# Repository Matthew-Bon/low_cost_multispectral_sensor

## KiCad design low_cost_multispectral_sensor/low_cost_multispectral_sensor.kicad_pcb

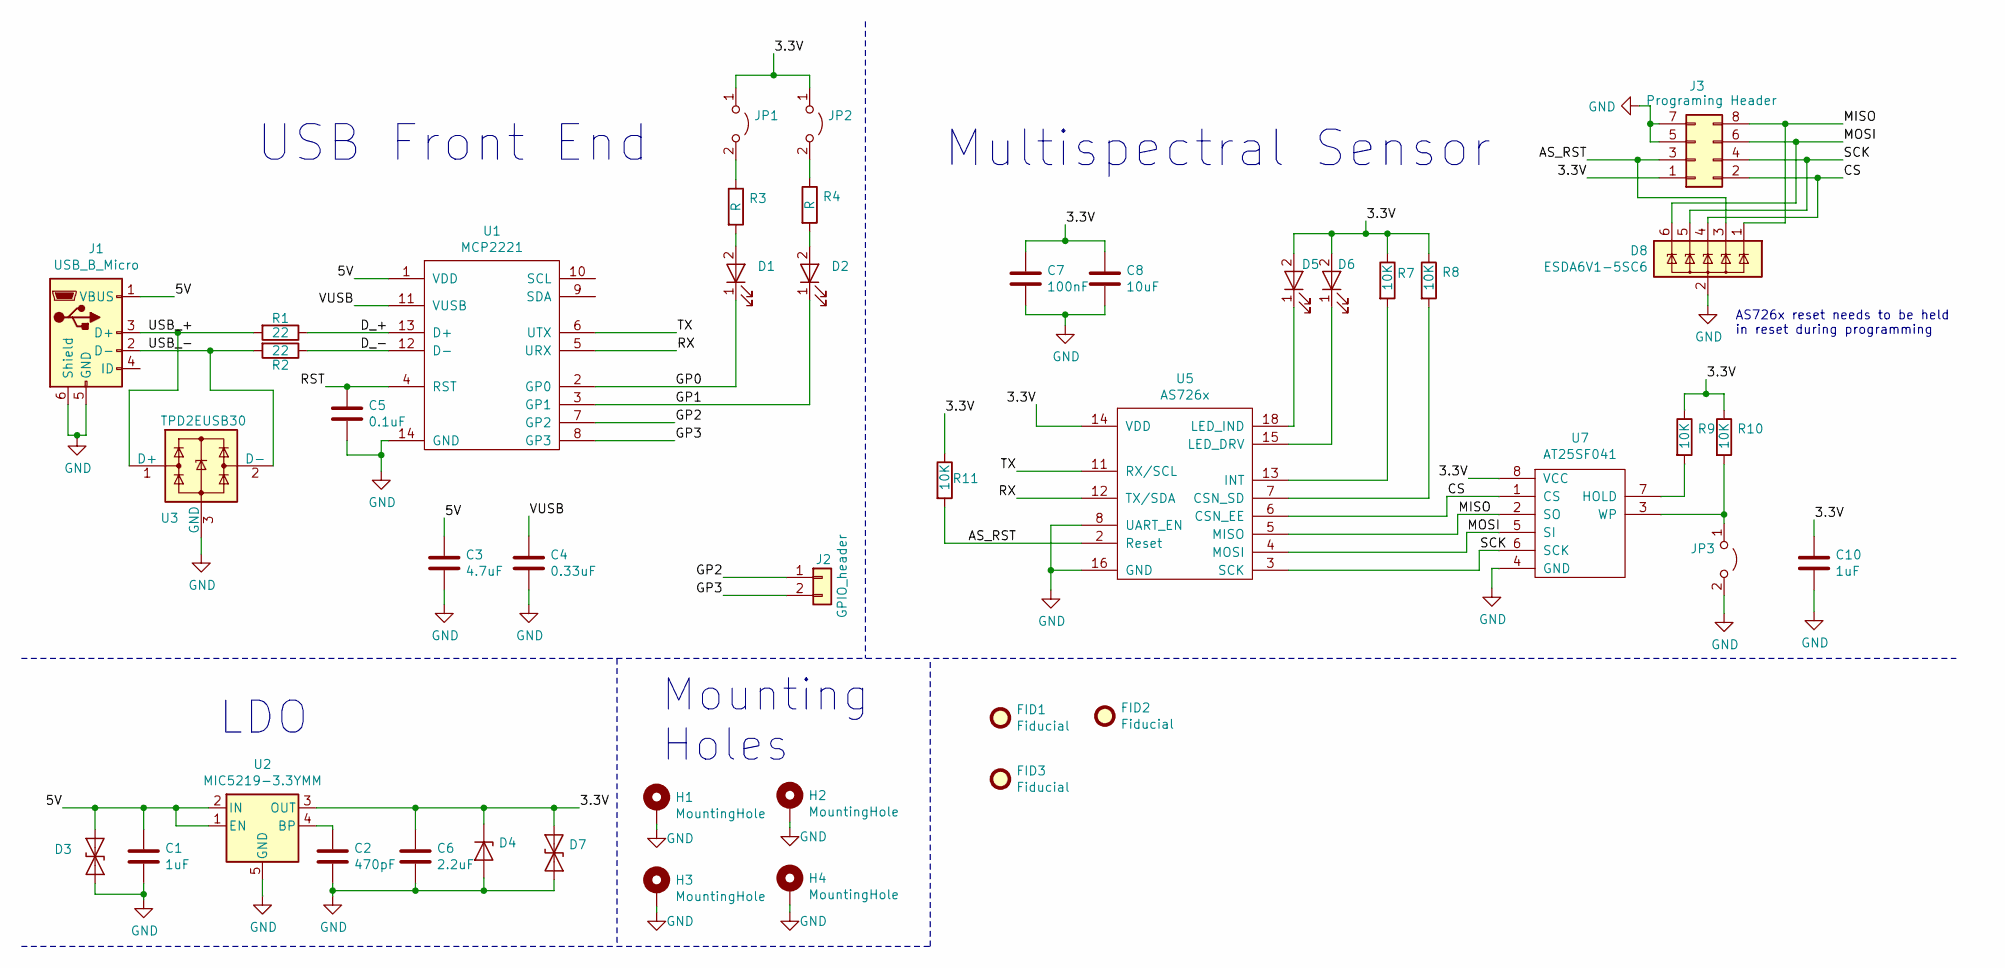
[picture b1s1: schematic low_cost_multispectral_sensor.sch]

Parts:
C1, C10: 1uF; C_0402
C2: 470pF; C_0402
C3: 4.7uF; C_0402
C4: 0.33uF; C_0402
C5: 0.1uF; C_0402
C6: 2.2uF; C_0402
C7: 100nF; C_0402
C8: 10uF; C_0402
D1: LTST-C191KRKT; D_0603
D2, D5: LTST-C191KGKT; D_0603
D3: VESD05A1-02V-G-08; D_SOD-523
D4: BZT585B3V3T-7; D_SOD-523
D6: L130-5780001400001; D_1206
D7: ESD5Z3.3T1G; D_SOD-523
D8: ESDA6V1-5SC6; SOT-23-6
FID1, FID2, FID3: Fiducial; Fiducial_1mm_Dia_2.54mm_Outer_CopperTop
H1, H2, H3, H4: MountingHole; MountingHole_2.2mm_M2_Pad
J1: USB_B_Micro; USB_Micro-B_Molex-105017-0001
J2: GPIO_header; Pin_Header_Straight_1x02_Pitch2.54mm
J3: Programing Header; Pin_Header_Straight_2x04_Pitch2.00mm
JP1, JP2, JP3: RC0402JR-070RL; R_0402
R1, R2: 22; R_0402
R3, R4: R; R_0402
R7, R8, R9, R10, R11: 10K; R_0402
U1: MCP2221; SOIC-14_N
U2: MIC5219-3.3YMM; SOT-23-5
U3: TPD2EUSB30; Texas_DRT-3
U5: AS726x
U7: AT25SF041; SOIC-8-N

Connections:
/3.3V: C6.1, C7.1, C8.1, C10.1, D4.1 (K), D5.2 (A), D6.2 (A), D7.1 (A1), J3.1, JP1.1 (A), JP2.1 (A), R7.1, R8.1, R9.1, R10.1, R11.1, U2.3 (OUT), U5.14 (VDD), U5.17 (VDD), U7.8 (VCC)
/5V: C1.1, C3.1, D3.1 (A1), J1.1 (VBUS), U1.1 (VDD), U2.1 (EN), U2.2 (IN)
/AS_RST: D8.3 (IO2), J3.3, R11.2, U5.2 (Reset)
/CS: D8.4 (IO3), J3.2, U5.6 (CSN_EE), U7.1 (CS)
/D_+: R1.1, U1.13 (D+)
/D_-: R2.1, U1.12 (D-)
/GP0: D1.1 (K), U1.2 (GP0)
/GP1: D2.1 (K), U1.3 (GP1)
/GP2: J2.1, U1.7 (GP2)
/GP3: J2.2, U1.8 (GP3)
/MISO: D8.1 (IO1), J3.8, U5.5 (MISO), U7.2 (SO)
/MOSI: D8.6 (IO5), J3.6, U5.4 (MOSI), U7.5 (SI)
/RST: C5.1, U1.4 (RST)
/RX: U1.5 (URX), U5.12 (TX/SDA)
/SCK: D8.5 (IO4), J3.4, U5.3 (SCK), U7.6 (SCK)
/TX: U1.6 (UTX), U5.11 (RX/SCL)
/USB_+: J1.3 (D+), R1.2, U3.1 (D+)
/USB_-: J1.2 (D-), R2.2, U3.2 (D-)
/VUSB: C4.1, U1.11 (VUSB)
GND: C1.2, C2.2, C3.2, C4.2, C5.2, C6.2, C7.2, C8.2, C10.2, D3.2 (A2), D4.2 (A), D7.2 (A2), D8.2 (GND), H1.1, H2.1, H3.1, H4.1, J1.5 (GND), J1.6 (Shield), J3.5, J3.7, JP3.2 (B), U1.14 (GND), U2.5 (GND), U2.6 (GND), U2.7 (GND), U2.8 (GND), U3.3 (GND), U5.8 (UART_EN), U5.16 (GND), U7.4 (GND)
unnamed: C2.1, U2.4 (BP)
unnamed: D1.2 (A), R3.2
unnamed: D2.2 (A), R4.2
unnamed: D5.1 (K), U5.18 (LED_IND)
unnamed: D6.1 (K), U5.15 (LED_DRV)
unnamed: JP1.2 (B), R3.1
unnamed: JP2.2 (B), R4.1
unnamed: JP3.1 (A), R10.2, U7.3 (WP)
unnamed: R7.2, U5.13 (INT)
unnamed: R8.2, U5.7 (CSN_SD)
unnamed: R9.2, U7.7 (HOLD)

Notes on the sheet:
LDO
USB Front End
Multispectral Sensor
AS726x reset needs to be held in reset during programming
Mounting Holes

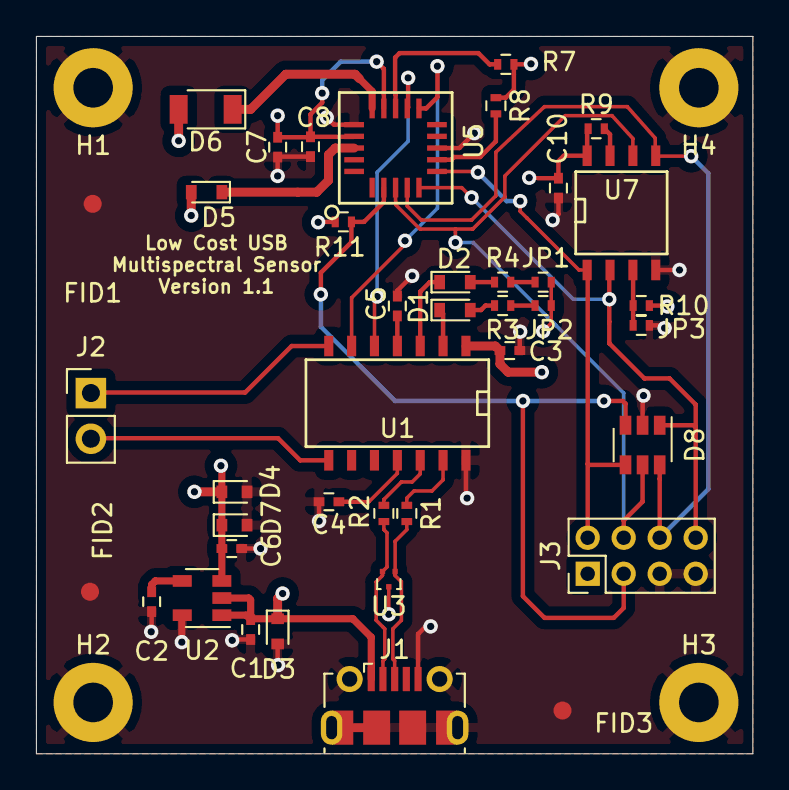
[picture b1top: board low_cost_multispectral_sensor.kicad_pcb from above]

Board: 4 copper layers, 39.8 x 39.8 mm, 44 parts (0 on the bottom side), 31 nets.

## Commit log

2019-10-16 fixed resets
2019-10-27 Updated schematic
2019-11-14 Initial layout completion
2020-09-24 Committed V1.1
